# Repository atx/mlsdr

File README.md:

# mlsdr
SDR for my TDOA radar project

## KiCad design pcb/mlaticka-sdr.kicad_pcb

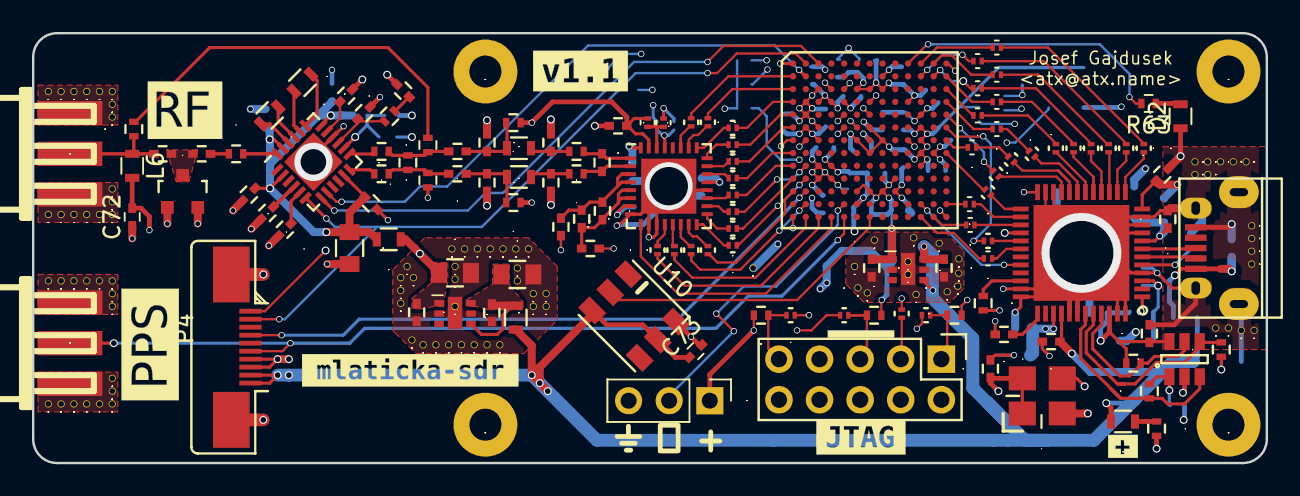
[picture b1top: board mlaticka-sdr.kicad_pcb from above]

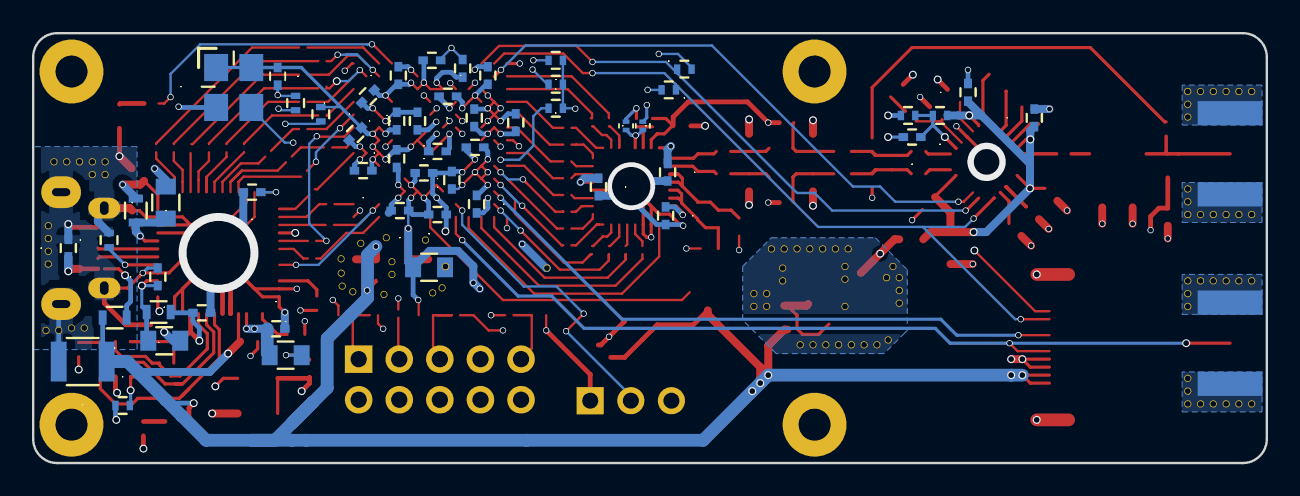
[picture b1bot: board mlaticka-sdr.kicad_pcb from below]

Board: 4 copper layers, 77.2 x 26.9 mm, 178 parts (54 on the bottom side), 140 nets.

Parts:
C1, C10: 330p; C_0402
C2, C18, C19, C42, C47, C51, C52: 1u; C_0402
C3, C4, C5, C6, C7, C9, C11, C12, C22, C23, C24, C25, C26, C29, C30, C31, C32, C36, C37, C38, C39, C40, C43, C44, C45, C46, C48, C49, C56, C57, C58, C59, C60, C61, C62, C63, C64, C65, C66, C67, C68, C69, C70, C71, C72, C73: 100n; C_0402
C8: 6n8; C_0402
C13, C14, C15, C16: DNP; C_0402
C17: 12p; C_0402
C20, C21: 2.2u; C_0402
C27, C54: 10n; C_0402
C28: 100u; C_1210
C33, C34, C35, C41, C50, C53, C55: 10u; C_0805
D1: LED_PWR; R_0603
D2: LED; R_0603
D3: BAV99; SOT-23
FB1: BEAD (1A); R_0603
FB2, FB3, FB4, FB5: BEAD (0.5A); R_0603
J1, J2: SMA; CON-SMA-EDGE
JP1, JP2: JMP_NO; R_0402
L1, L3: 150n; R_0603
L2: 8n2; R_0402
L4, L5: JMP; R_0603
L6: 220n; R_0603
P1: USB_OTG; USB_Micro-B
P2: JTAG; Pin_Header_Straight_2x05
P3: CONN_CLK_EXT; Pin_Header_Straight_1x03_Pitch2.54mm
P4: CONN_EXT; SFV10R
R1: 1k8; R_0402
R2, R3: 1k; R_0402
R4, R5: 25; R_0402
R6, R48: 0; R_0201
R7, R74: DNP; R_0201
R8, R9: 0; R_0402
R10, R27: DNP; R_0402
R11: 33k; R_0402
R12: 20k; R_0402
R13, R14, R15, R16, R17, R18, R19, R20, R21, R22, R23, R24, R25, R26, R36, R37, R38, R39, R40, R41, R42, R43, R44, R45, R46, R50, R51, R52, R53: 33; R_0201
R28, R29, R31, R34, R54, R55, R56, R57, R58: 10k; R_0402
R30: 2k; R_0402
R32, R33, R65, R66, R67, R68, R69, R70, R71, R72, R73: 33R; R_0201
R35: 12k; R_0402
R47, R63: R; R_0402
R49, R59, R60, R61, R62: 5k1; R_0402
U1: R820T; QFN-24_4x4mm_Pitch0.5mm_NoMask
U2: LTC22xx; QFN-32-1EP_5x5mm_Pitch0.5mm
U3: 93LC56BT; SOT-23-6
U4: FT232H; QFN-48-1EP_8x8mm_Pitch0.5mm
U5: ASFL1-12.000MHZ-EK-T; ABRACON-ASFL1
U6: 10M08SCU169; UBGA-169
U7, U8: LP5912-3.3; WSON-6-DRV
U9: ASFL1-30.000MHZ-EK-T; ABRACON-ASFL1
U10: WS2812

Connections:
3.3V_A: C23.1, C24.1, C25.1, C52.1, C53.1, FB5.1, R6.1, R74.2, U2.7, U2.21, U2.32, U8.1
3.3V_FPGA: C41.1, C43.1, C44.1, C45.1, C46.1, C47.1, C48.1, C49.1, C56.1, C57.1, C58.1, C59.1, C60.1, C61.1, C62.1, C63.1, C64.1, C65.1, C66.1, C67.1, C68.1, C69.1, C71.1, P2.4, P3.1, R49.1, R54.2, R55.1, R56.1, R57.1, R60.2, R61.2, R62.1, U6.C6, U6.C7, U6.C8, U6.D3, U6.D4, U6.D10, U6.F2, U6.F7, U6.F11, U6.G3, U6.G6, U6.G8, U6.G11, U6.H7, U6.H11, U6.J3, U6.J11, U6.K3, U6.K4, U6.K9, U6.L6, U6.L7, U6.L8, U7.1, U9.1, U9.4
+5V: C28.1, C29.1, C42.1, C72.2, C73.1, D1.2, FB1.2, FB4.1, L6.2, P4.9, P4.10, U4.40, U7.4, U7.6, U10.3, U10.5
/ADC/BYPASS: JP1.2, R27.2
/ADC/VCM: C21.1, R2.1, R3.1, R48.1, U2.31
/FPGA-Misc/TCK: P2.1, R52.2, R59.1
/FPGA-Misc/TDI: P2.9, R51.2, R61.1
/FPGA-Misc/TDO: P2.3, R50.2
/FPGA-Misc/TMS: P2.5, R53.2, R60.1
/FPGA/30Mhz: U6.G10, U9.3
/FPGA/ADC_CLK: U2.9, U6.N4
/FPGA/ADC_D0: R13.1, U6.N3
/FPGA/ADC_D1: R14.1, U6.N2
/FPGA/ADC_D2: R15.1, U6.M2
/FPGA/ADC_D3: R16.1, U6.L1
/FPGA/ADC_D4: R17.1, U6.K2
/FPGA/ADC_D5: R18.1, U6.K1
/FPGA/ADC_D6: R19.1, U6.J2
/FPGA/ADC_D7: R20.1, U6.J1
/FPGA/ADC_D8: R21.1, U6.H1
/FPGA/ADC_D9: R22.1, U6.F1
/FPGA/ADC_D10: R23.1, U6.E1
/FPGA/ADC_D11: R24.1, U6.D1
/FPGA/ADC_D12: R25.1, U6.C1
/FPGA/ADC_D13: R26.1, U6.B1
/FPGA/CLK_EXT: P3.2, U6.M5
/FPGA/EXT_P1: P4.4, U6.L2
/FPGA/FT_D0: R70.2, U6.A11
/FPGA/FT_D1: R69.2, U6.B11
/FPGA/FT_D2: R68.2, U6.A12
/FPGA/FT_D3: R67.2, U6.B12
/FPGA/FT_D4: R66.2, U6.B13
/FPGA/FT_D5: R65.2, U6.C13
/FPGA/FT_D6: R33.2, U6.D13
/FPGA/FT_D7: R32.2, U6.G13
/FPGA/FT_RST: U4.32, U6.M11
/FPGA/FT_~OE: R73.1, U4.30
/FPGA/FT_~RD: R71.1, U4.26
/FPGA/FT_~RXF: R44.1, U6.E13
/FPGA/FT_~TXE: R45.1, U6.H13
/FPGA/FT_~WR: R72.1, U4.27
/FPGA/LED_DATA: U6.N7, U10.2
/FPGA/PPS: J2.1, P4.6, U6.N5
/FPGA/SCL: P4.2, R62.2, U1.6, U6.A2
/FPGA/SDA: P4.1, R49.2, U1.7, U6.A3
/FTDI/3.3V_FT: C26.1, C31.1, C32.1, C35.1, C36.1, C39.1, C40.1, FB2.1, FB3.1, R28.1, R29.1, R31.1, R34.2, U3.6, U4.12, U4.24, U4.28, U4.39, U4.46, U5.1, U5.4
/FTDI/12MHz: U4.1, U5.3
/FTDI/CLK: R46.1, U6.F13
/FTDI/D0: R36.1, R70.1
/FTDI/D1: R37.1, R69.1
/FTDI/D2: R38.1, R68.1
/FTDI/D3: R39.1, R67.1
/FTDI/D4: R40.1, R66.1
/FTDI/D5: R41.1, R65.1
/FTDI/D6: R33.1, R42.1
/FTDI/D7: R32.1, R43.1
/FTDI/VCCA: C30.1, U4.37
/FTDI/VPHY: C33.1, C37.1, FB2.2, U4.3
/FTDI/VPLL: C34.1, C38.1, FB3.2, U4.8
/RF/3.3V: C4.1, C5.1, C7.1, C9.1, C55.1, FB5.2, R11.1, U1.2, U1.11, U1.18, U1.23
/RF/CLK: U1.8, U6.B2
/RF/IF_N: C12.2, JP2.2, R8.1, R10.1
/RF/IF_P: C11.2, JP1.1, R9.1, R10.2
GND: C2.2, C3.2, C4.2, C5.2, C6.2, C7.2, C8.2, C9.2, C10.2, C13.1, C14.2, C15.1, C16.2, C18.2, C19.2, C21.2, C23.2, C24.2, C25.2, C26.2, C27.2, C28.2, C29.2, C30.2, C31.2, C32.2, C33.2, C34.2, C35.2, C36.2, C37.2, C38.2, C39.2, C40.2, C41.2, C42.2, C43.2, C44.2, C45.2, C46.2, C47.2, C48.2, C49.2, C50.2, C51.2, C52.2, C53.2, C55.2, C56.2, C57.2, C58.2, C59.2, C60.2, C61.2, C62.2, C63.2, C64.2, C65.2, C66.2, C67.2, C68.2, C69.2, C70.2, C71.2, C72.1, C73.2, D2.1, D3.1, D3.2, J1.2, J1.3, J1.4, J1.5, J2.2, J2.3, J2.4, J2.5, JP2.1, P1.5, P1.6, P2.2, P2.10, P3.3, P4.7, P4.8, P4.11, R7.2, R12.2, R35.2, R47.2, R58.1, R59.2, U1.16, U1.25, U2.8, U2.10, U2.11, U2.20, U2.33, U3.2, U4.4, U4.9, U4.10, U4.11, U4.22, U4.23, U4.35, U4.36, U4.41, U4.42, U4.47, U4.48, U4.49, U5.2, U6.A1, U6.A13, U6.B8, U6.C3, U6.D2, U6.D5, U6.E2, U6.E11, U6.F3, U6.G7, U6.H12, U6.J4, U6.L9, U6.M6, U6.N1, U6.N13, U7.2, U7.5, U8.2, U8.5, U9.2, U10.6
unnamed: C1.1, L2.1
unnamed: C1.2, C54.1, D3.3
unnamed: C2.1, U1.4
unnamed: C3.1, U1.5
unnamed: C6.1, U1.17
unnamed: C8.1, R1.2
unnamed: C10.1, R1.1, U1.15
unnamed: C11.1, C13.2, L4.2, R2.2
unnamed: C12.1, C14.1, L5.1, R3.2
unnamed: C15.2, L4.1, R4.2
unnamed: C16.1, L5.2, R5.2
unnamed: C17.1, R4.1, U2.1
unnamed: C17.2, R5.1, U2.2
unnamed: C18.1, C20.1, C22.1, U2.3, U2.4
unnamed: C19.1, C20.2, C22.2, U2.5, U2.6
unnamed: C27.1, FB1.1, P1.1
unnamed: C50.1, C51.1, FB4.2, U8.4, U8.6
unnamed: C54.2, J1.1, L6.1, R27.1
unnamed: C70.1, R11.2, R12.1, U1.14
unnamed: D1.1, R47.1
unnamed: D2.2, R63.1
unnamed: L1.1, U1.19
unnamed: L1.2, U1.20
unnamed: L2.2, U1.24
unnamed: L3.1, U1.21
unnamed: L3.2, U1.22
unnamed: P1.2, U4.6
unnamed: P1.3, U4.7
unnamed: R6.2, R7.1, U2.29
unnamed: R8.2, U1.12
unnamed: R9.2, U1.13
unnamed: R13.2, U2.12
unnamed: R14.2, U2.13
unnamed: R15.2, U2.14
unnamed: R16.2, U2.15
unnamed: R17.2, U2.16
unnamed: R18.2, U2.17
unnamed: R19.2, U2.18
unnamed: R20.2, U2.19
unnamed: R21.2, U2.22
unnamed: R22.2, U2.23
unnamed: R23.2, U2.24
unnamed: R24.2, U2.25
unnamed: R25.2, U2.26
unnamed: R26.2, U2.27
unnamed: R28.2, R30.2, U3.1
unnamed: R29.2, U3.4, U4.44
unnamed: R30.1, U3.3, U4.43
unnamed: R31.2, U3.5, U4.45
unnamed: R34.1, U4.34
unnamed: R35.1, U4.5
unnamed: R36.2, U4.13
unnamed: R37.2, U4.14
unnamed: R38.2, U4.15
unnamed: R39.2, U4.16
unnamed: R40.2, U4.17
unnamed: R41.2, U4.18
unnamed: R42.2, U4.19
unnamed: R43.2, U4.20
unnamed: R44.2, U4.21
unnamed: R45.2, U4.25
unnamed: R46.2, U4.29
unnamed: R48.2, R74.1, U2.30
unnamed: R50.1, U6.F6
unnamed: R51.1, U6.F5
unnamed: R52.1, U6.G2
unnamed: R53.1, U6.G1
unnamed: R54.1, U6.E5
unnamed: R55.2, U6.C5
unnamed: R56.2, U6.C4
unnamed: R57.2, U6.E7
unnamed: R58.2, U6.D7
unnamed: R63.2, U6.A10
unnamed: R71.2, U6.M13
unnamed: R72.2, U6.N12
unnamed: R73.2, U6.N11

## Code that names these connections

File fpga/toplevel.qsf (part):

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set_global_assignment -name EDA_SIMULATION_TOOL "ModelSim-Altera (Verilog)"
set_global_assignment -name EDA_TIME_SCALE "1 ps" -section_id eda_simulation
set_global_assignment -name EDA_OUTPUT_DATA_FORMAT "VERILOG HDL" -section_id eda_simulation
set_location_assignment PIN_N4 -to ADC_CLK
set_location_assignment PIN_A12 -to FT_D2
set_instance_assignment -name IO_STANDARD "3.3-V LVCMOS" -to FT_D2
set_location_assignment PIN_B13 -to FT_D4
set_instance_assignment -name IO_STANDARD "3.3-V LVCMOS" -to FT_D4
set_instance_assignment -name IO_STANDARD "3.3-V LVCMOS" -to ADC_CLK
set_location_assignment PIN_C13 -to FT_D5
set_instance_assignment -name IO_STANDARD "3.3-V LVCMOS" -to FT_D5
set_location_assignment PIN_B11 -to FT_D1
set_instance_assignment -name IO_STANDARD "3.3-V LVCMOS" -to FT_D1
set_location_assignment PIN_B12 -to FT_D3
set_instance_assignment -name IO_STANDARD "3.3-V LVCMOS" -to FT_D3
set_location_assignment PIN_D13 -to FT_D6
set_instance_assignment -name IO_STANDARD "3.3-V LVCMOS" -to FT_D6
set_location_assignment PIN_G13 -to FT_D7
set_instance_assignment -name IO_STANDARD "3.3-V LVCMOS" -to FT_D7
set_location_assignment PIN_E13 -to FT_nRXF
set_instance_assignment -name IO_STANDARD "3.3-V LVCMOS" -to FT_nRXF
set_location_assignment PIN_F13 -to FT_CLK
set_instance_assignment -name IO_STANDARD "3.3-V LVCMOS" -to FT_CLK
set_location_assignment PIN_A11 -to FT_D0
set_instance_assignment -name IO_STANDARD "3.3-V LVCMOS" -to FT_D0
set_location_assignment PIN_H13 -to FT_nTXE
set_instance_assignment -name IO_STANDARD "3.3-V LVCMOS" -to FT_nTXE
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set_instance_assignment -name IO_STANDARD "3.3-V LVCMOS" -to FT_nWR
set_location_assignment PIN_N11 -to FT_nOE
set_instance_assignment -name IO_STANDARD "3.3-V LVCMOS" -to FT_nOE
set_location_assignment PIN_M11 -to FT_RST
set_instance_assignment -name IO_STANDARD "3.3-V LVCMOS" -to FT_RST
set_location_assignment PIN_H1 -to ADC_D8
set_instance_assignment -name IO_STANDARD "3.3-V LVCMOS" -to ADC_D8
set_instance_assignment -name RESERVE_PIN AS_INPUT_TRI_STATED -to ADC_D8
set_location_assignment PIN_E1 -to ADC_D10
set_instance_assignment -name IO_STANDARD "3.3-V LVCMOS" -to ADC_D10
set_instance_assignment -name RESERVE_PIN AS_INPUT_TRI_STATED -to ADC_D10
set_location_assignment PIN_F1 -to ADC_D9
set_instance_assignment -name IO_STANDARD "3.3-V LVCMOS" -to ADC_D9
set_instance_assignment -name RESERVE_PIN AS_INPUT_TRI_STATED -to ADC_D9
set_location_assignment PIN_B1 -to ADC_D13
set_instance_assignment -name IO_STANDARD "3.3-V LVCMOS" -to ADC_D13
set_instance_assignment -name RESERVE_PIN AS_INPUT_TRI_STATED -to ADC_D13
set_location_assignment PIN_D1 -to ADC_D11
set_instance_assignment -name IO_STANDARD "3.3-V LVCMOS" -to ADC_D11
set_instance_assignment -name RESERVE_PIN AS_INPUT_TRI_STATED -to ADC_D11
set_location_assignment PIN_K2 -to ADC_D4
set_instance_assignment -name IO_STANDARD "3.3-V LVCMOS" -to ADC_D4
set_instance_assignment -name RESERVE_PIN AS_INPUT_TRI_STATED -to ADC_D4
set_location_assignment PIN_K1 -to ADC_D5
set_instance_assignment -name IO_STANDARD "3.3-V LVCMOS" -to ADC_D5
set_instance_assignment -name RESERVE_PIN AS_INPUT_TRI_STATED -to ADC_D5
set_location_assignment PIN_M2 -to ADC_D2
set_instance_assignment -name IO_STANDARD "3.3-V LVCMOS" -to ADC_D2
set_instance_assignment -name RESERVE_PIN AS_INPUT_TRI_STATED -to ADC_D2
set_location_assignment PIN_N5 -to PPS
set_instance_assignment -name IO_STANDARD "3.3-V LVCMOS" -to PPS
set_location_assignment PIN_L1 -to ADC_D3
set_instance_assignment -name IO_STANDARD "3.3-V LVCMOS" -to ADC_D3
set_instance_assignment -name RESERVE_PIN AS_INPUT_TRI_STATED -to ADC_D3
set_location_assignment PIN_N3 -to ADC_D0
set_instance_assignment -name IO_STANDARD "3.3-V LVCMOS" -to ADC_D0
set_instance_assignment -name RESERVE_PIN AS_INPUT_TRI_STATED -to ADC_D0
set_location_assignment PIN_N2 -to ADC_D1
set_instance_assignment -name IO_STANDARD "3.3-V LVCMOS" -to ADC_D1
set_instance_assignment -name RESERVE_PIN AS_INPUT_TRI_STATED -to ADC_D1
set_location_assignment PIN_J2 -to ADC_D6
set_instance_assignment -name IO_STANDARD "3.3-V LVCMOS" -to ADC_D6
set_instance_assignment -name RESERVE_PIN AS_INPUT_TRI_STATED -to ADC_D6
set_location_assignment PIN_J1 -to ADC_D7
set_instance_assignment -name IO_STANDARD "3.3-V LVCMOS" -to ADC_D7
set_instance_assignment -name RESERVE_PIN AS_INPUT_TRI_STATED -to ADC_D7
set_global_assignment -name PARTITION_NETLIST_TYPE SOURCE -section_id Top
set_global_assignment -name PARTITION_FITTER_PRESERVATION_LEVEL PLACEMENT_AND_ROUTING -section_id Top
set_global_assignment -name PARTITION_COLOR 16764057 -section_id Top
set_location_assignment PIN_M5 -to CLK_EXT
set_instance_assignment -name IO_STANDARD "3.3-V LVCMOS" -to CLK_EXT
set_location_assignment PIN_B2 -to TUNER_CLK
set_instance_assignment -name IO_STANDARD "3.3-V LVCMOS" -to TUNER_CLK
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set_global_assignment -name OUTPUT_IO_TIMING_FAR_END_VMEAS "HALF SIGNAL SWING" -rise
set_global_assignment -name OUTPUT_IO_TIMING_FAR_END_VMEAS "HALF SIGNAL SWING" -fall
set_global_assignment -name POWER_USE_INPUT_FILES OFF
set_location_assignment PIN_C1 -to ADC_D12
set_instance_assignment -name IO_STANDARD "3.3-V LVCMOS" -to ADC_D12
set_instance_assignment -name RESERVE_PIN AS_INPUT_TRI_STATED -to ADC_D12
set_location_assignment PIN_L2 -to EXT_P1
set_instance_assignment -name IO_STANDARD "3.3-V LVCMOS" -to EXT_P1
set_instance_assignment -name RESERVE_PIN AS_BIDIRECTIONAL -to EXT_P1
set_instance_assignment -name IO_STANDARD "3.3-V LVCMOS" -to LED_DATA
set_location_assignment PIN_N7 -to LED_DATA
set_instance_assignment -name RESERVE_PIN AS_OUTPUT_DRIVING_AN_UNSPECIFIED_SIGNAL -to LED_DATA
set_instance_assignment -name RESERVE_PIN AS_INPUT_TRI_STATED -to FT_nRXF
set_instance_assignment -name RESERVE_PIN AS_INPUT_TRI_STATED -to FT_nTXE
set_instance_assignment -name RESERVE_PIN AS_INPUT_TRI_STATED -to FT_RST
set_global_assignment -name POWER_PRESET_COOLING_SOLUTION "23 MM HEAT SINK WITH 200 LFPM AIRFLOW"
set_global_assignment -name POWER_BOARD_THERMAL_MODEL "NONE (CONSERVATIVE)"
set_global_assignment -name FLOW_ENABLE_POWER_ANALYZER ON
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
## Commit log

2017-07-11 Initial import from the main repo
2017-07-11 fpga: Modify pins to match the v1.1 board
    Note that this intentionally breaks the build
2017-07-14 pcb: Update to the v1.1 version
    Turns out that I forgot to commit these in the old repository
2017-07-23 lib: Report mismatching bytes in the ID sequence
2017-07-23 lib: mlsdr_sdr: Properly handle boards without r820t specified
2017-07-23 fpga: pll: Switch to the 30MHz oscillator on v1.1 board
2017-07-23 fpga: Start with chisel rewrite
    This also includes a bunch of hard-to-separate changes for the v1.1 board.
2017-07-26 lib: Log after initialization is complete
2017-07-27 fpga: Add sawtooth pattern switch
2017-07-27 lib: mlsdr_test: Add sawtooth checking binary
2017-07-27 lib: Warn on samples lost in the sample ring buffer
2017-07-27 lib: ring: Fix off-by-one error leading to dropped samples
2017-07-27 lib: mlsdr_test: Output the in-chunk iterator value on error
    Really helped with debugging 7ddf5fb
2017-07-29 lib: mlsdr_test: Drop leftover debug print
2017-07-29 fpga: Move some of the registers to Scala
2017-07-29 lib: mlsdr_test: Properly timeout and terminate if no samples arrive
2017-07-29 fpga: Run at 90MHz
    The FPGA is getting worryingly hot (> 50C) and we don't really need that speed
    anyway (though note that it might be good idea to increase again for PPS
    sampling)
2017-07-29 fpga: Move ADC divisor to Config (and calculate automatically)
2017-07-29 fpga: Make special type of register for constant values
    Not that it helps with performance much, but it definitely looks better
2017-07-30 fpga: Rewrite the config registers in Chisel
    I2C still uses the Verilog ones, but that will hopefully change soon
2017-07-30 lib: mlsdr_test: Add scratchpad read/write test
    Also restructured to be prepared for inclusion of more tests.
2017-07-30 fpga: Rewrite packer in chisel
2017-07-31 lib: mlsdr_sdr: Add -o option to specify the output file
2017-07-31 lib: mlsdr_test: Quick and hacky sample rate checking

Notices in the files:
fpga/toplevel.qsf:
Copyright (C) 2016  Intel Corporation. All rights reserved.
